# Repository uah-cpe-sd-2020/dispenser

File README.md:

# dispenser
Code for the embedded controller at the feeder

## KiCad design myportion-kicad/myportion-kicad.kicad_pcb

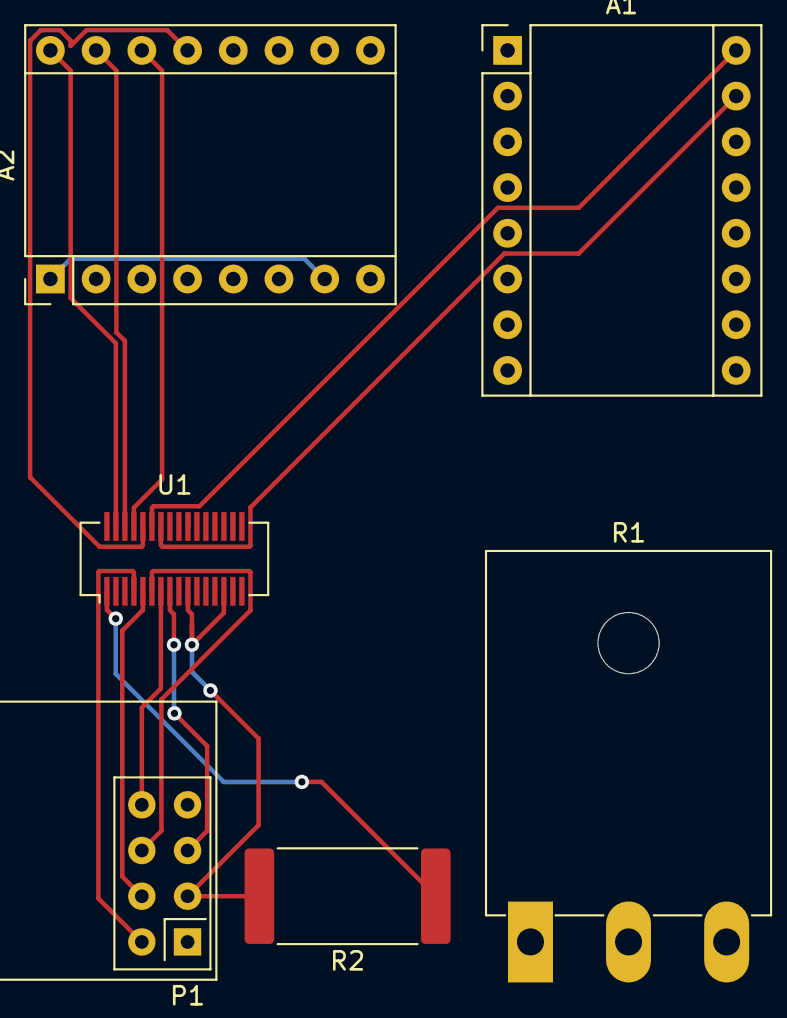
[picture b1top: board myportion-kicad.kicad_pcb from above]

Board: 2 copper layers, 6 parts (0 on the bottom side), 19 nets.

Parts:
A1, A2: Pololu_Breakout_A4988; Pololu_Breakout-16_15.2x20.3mm
P1: RFID-RC522-MODULE; nRF24L01_Breakout
R1: R_Variable; TO-3PB-3_Horizontal_TabDown
R2: R; R_4020_10251Metric_Pad1.65x5.30mm_HandSolder
U1: NodeMCU_1.0_(ESP-12E); Hirose_DF12_DF12E3.0-32DP-0.5V_2x16_P0.50mm_Vertical

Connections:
+3V3: R1.1, U1.15
+12V: A1.8, A2.8
GND: A1.1, A1.7, A2.1, A2.7, P1.3, R2.2, U1.10, U1.14
unnamed: A1.13, U1.27
unnamed: A1.14, U1.26
unnamed: A1.15, U1.23
unnamed: A1.16, U1.22
unnamed: A2.13, U1.21
unnamed: A2.14, U1.20
unnamed: A2.15, U1.19
unnamed: A2.16, U1.18
unnamed: P1.1, U1.11
unnamed: P1.2, U1.4
unnamed: P1.4, U1.5
unnamed: P1.5, U1.8
unnamed: P1.6, U1.6
unnamed: P1.7, U1.9
unnamed: P1.8, U1.7
unnamed: R1.2, R2.1, U1.1

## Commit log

2021-01-28 Add Hardware Documentation.
    Add hardware.md
    Put initial planned hardware
    Make sure we have enough pins
    Add Links & images
2021-01-28 Add Pinout of RC522
2021-01-28 Add Photo Electric Switch Pinout
2021-01-28 Add Stepper Motor Driver Pinouts.
    - Move PES
    - Add all Stepper Motor Drivers
2021-01-28 Add NodeMCU Documentation
2021-01-29 Add kicad project
2021-02-12 Add rough kicad project
2021-02-12 Create a bare project from PIO in VSCode
2021-02-12 Update with flashing light code.
2021-02-12 Define pinouts in pinout.h
2021-02-12 Create Functions to move the Auger motor
2021-02-12 Add sensing from the PES
2021-02-18 Move includes to the include directory. Troubleshooting serial setup.
2021-02-18 Move motor code into individual includes. Update pinout. No longer functional...
2021-02-19 Update pinout to tie motors together.
    This allows for individual control of each motor via stepping,
    but removes individual control over direction, slp, and rst pins.
2021-02-19 Add the essential Sleep command to keep motors from overheating.
2021-02-24 Closes #4
    RFID Scanning is functional and triggers an interrupt
2021-02-24 Update Pinouts in Documentation
2021-02-24 Remove debug statement
2021-03-03 Add Wifi Capability
2021-03-03 Update Wifi include styling
2021-03-03 Update to use DHCP to acquire IP as client.
2021-03-03 Add method to test name resolution through DNS. Success :)
2021-03-03 Add boot delay to see full serial output
2021-03-03 Redirect All DNS to Portal
    - Portal is defaulting to 192.168.4.1 as We don't have control over the
    DNS forwarding all traffic to that address... So we're rolling with it.
    - Add [WM] to the beginning of all non-debug messages
    - Change Debug level to 0 to silence output during other testing
2021-03-30 Generate some working functions to make it possible to process the schedules
2021-04-18 Add Images
